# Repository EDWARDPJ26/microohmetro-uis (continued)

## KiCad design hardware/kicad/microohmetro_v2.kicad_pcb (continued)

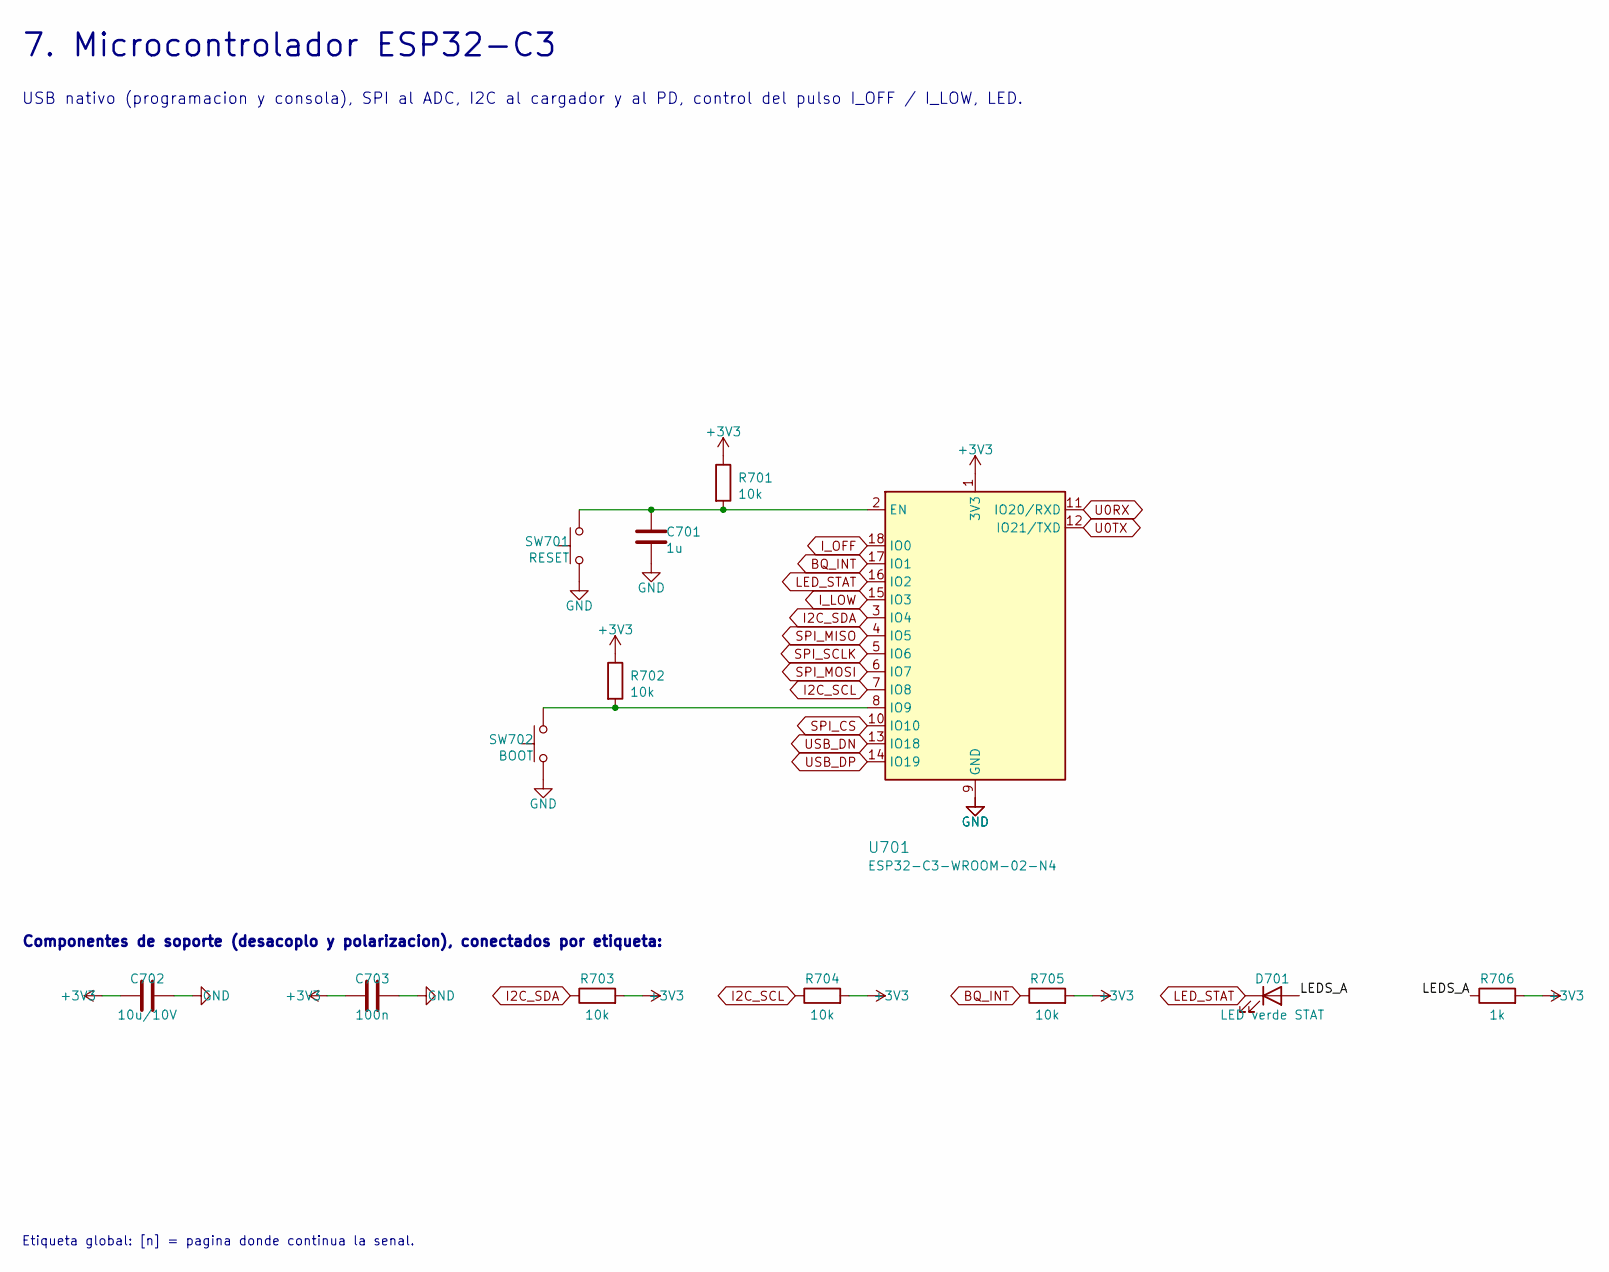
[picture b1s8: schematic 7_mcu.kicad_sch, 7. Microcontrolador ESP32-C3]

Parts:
C701: 1u; C_0603_1608Metric
C702: 10u/10V; C_0805_2012Metric
C703: 100n; C_0603_1608Metric
D701: LED verde STAT; LED_0603_1608Metric
R701, R702, R703, R704, R705: 10k; R_0603_1608Metric
R706: 1k; R_0603_1608Metric
SW701: RESET; SW_Push_SPST_NO_Alps_SKRK
SW702: BOOT; SW_Push_SPST_NO_Alps_SKRK
U701: ESP32-C3-WROOM-02-N4; ESP32-C3-WROOM-02; MPN ESP32-C3-WROOM-02-N4

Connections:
+3V3: C702.1, C703.1, R701.1, R702.1, R703.2, R704.2, R705.2, R706.2, U701.1 (3V3); also elsewhere on the board
BQ_INT: R705.1, U701.17 (IO1); also elsewhere on the board
GND: C701.2, C702.2, C703.2, SW701.1, SW702.1, U701.9 (GND), U701.19 (GND); also elsewhere on the board
I2C_SCL: R704.1, U701.7 (IO8); also elsewhere on the board
I2C_SDA: R703.1, U701.3 (IO4); also elsewhere on the board
I_LOW: U701.15 (IO3); also elsewhere on the board
I_OFF: U701.18 (IO0); also elsewhere on the board
LEDS_A: D701.2 (A), R706.1
LED_STAT: D701.1 (K), U701.16 (IO2)
unnamed: C701.1, R701.2, SW701.2, U701.2 (EN)
unnamed: R702.2, SW702.2, U701.8 (IO9)
SPI_CS: U701.10 (IO10); also elsewhere on the board
SPI_MISO: U701.4 (IO5); also elsewhere on the board
SPI_MOSI: U701.6 (IO7); also elsewhere on the board
SPI_SCLK: U701.5 (IO6); also elsewhere on the board
U0RX: U701.11 (IO20/RXD); also elsewhere on the board
U0TX: U701.12 (IO21/TXD); also elsewhere on the board
USB_DN: U701.13 (IO18); also elsewhere on the board
USB_DP: U701.14 (IO19); also elsewhere on the board

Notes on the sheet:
7. Microcontrolador ESP32-C3
USB nativo (programacion y consola), SPI al ADC, I2C al cargador y al PD, control del pulso I_OFF / I_LOW, LED.
Componentes de soporte (desacoplo y polarizacion), conectados por etiqueta:
Etiqueta global: [n] = pagina donde continua la senal.

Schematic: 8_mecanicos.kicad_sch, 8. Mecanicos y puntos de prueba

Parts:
H801, H802, H803, H804: M3; MountingHole_3.2mm_M3
TP801: TP U0TX; TestPoint_Pad_D1.5mm
TP802: TP U0RX; TestPoint_Pad_D1.5mm
TP803: TP GND; TestPoint_Pad_D1.5mm
TP804: TP SYS; TestPoint_Pad_D1.5mm
TP805: TP VBAT_CHG; TestPoint_Pad_D1.5mm
TP806: TP AVDD; TestPoint_Pad_D1.5mm

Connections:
AVDD: TP806.1; also elsewhere on the board
GND: TP803.1; also elsewhere on the board
SYS: TP804.1; also elsewhere on the board
U0RX: TP802.1; also elsewhere on the board
U0TX: TP801.1; also elsewhere on the board
VBAT_CHG: TP805.1; also elsewhere on the board

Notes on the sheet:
8. Mecanicos y puntos de prueba
Agujeros M3, puntos de prueba y bandera de GND.
Etiqueta global: [n] = pagina donde continua la senal.

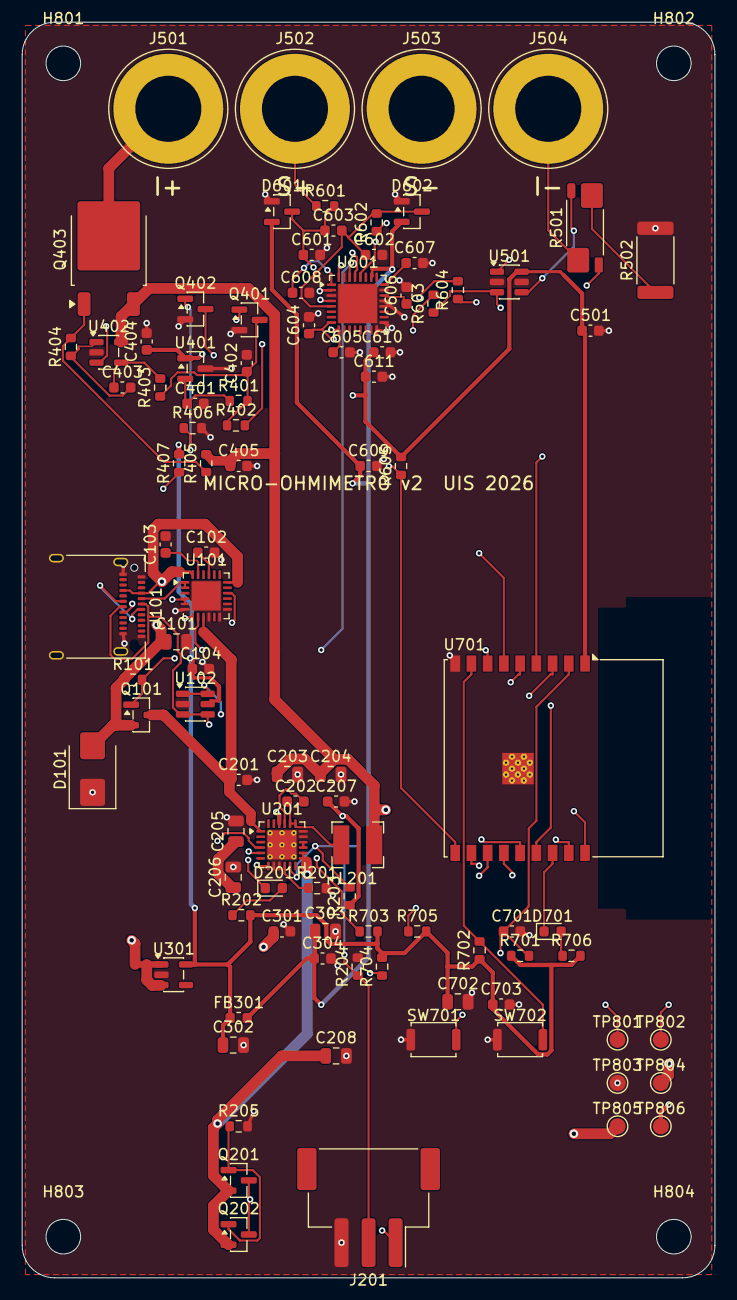
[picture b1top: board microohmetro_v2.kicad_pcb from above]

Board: 4 copper layers, 64.0 x 116.0 mm, 103 parts (1 on the bottom side), 60 nets.

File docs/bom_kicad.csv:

"Reference","Value","Footprint","MPN","Description","QUANTITY"
"C101,C205,C206","10u/25V","Capacitor_SMD:C_0805_2012Metric","","X7R","3"
"C102-C104,C301,C401,C609,C610,C701","1u","Capacitor_SMD:C_0603_1608Metric","","X7R","8"
"C201","1u/25V","Capacitor_SMD:C_0603_1608Metric","","X7R","1"
"C202","47n","Capacitor_SMD:C_0603_1608Metric","","X7R","1"
"C203,C204,C208,C302,C303,C702","10u/10V","Capacitor_SMD:C_0805_2012Metric","","X7R","6"
"C207","4.7u/10V","Capacitor_SMD:C_0603_1608Metric","","X7R","1"
"C304,C404,C405,C501,C606-C608,C611,C703","100n","Capacitor_SMD:C_0603_1608Metric","","X7R","9"
"C402","22n","Capacitor_SMD:C_0603_1608Metric","","C0G (arranque suave)","1"
"C403,C603","10n","Capacitor_SMD:C_0603_1608Metric","","C0G (integrador),C0G diferencial","2"
"C601,C602,C604,C605","1n","Capacitor_SMD:C_0603_1608Metric","","C0G","4"
"D101","SMBJ12A","Diode_SMD:D_SMB","SMBJ12A","TVS 12 V","1"
"D201","LED ambar CHG","LED_SMD:LED_0603_1608Metric","","Indicador de carga","1"
"D601,D602","BAT54S","Package_TO_SOT_SMD:SOT-23","BAT54S","Clamp AIN0,Clamp AIN1","2"
"D701","LED verde STAT","LED_SMD:LED_0603_1608Metric","","","1"
"FB301","600R@100MHz","Inductor_SMD:L_0603_1608Metric","BLM18KG601SN1D","Ferrita de aislamiento analogico","1"
"H801-H804","M3","MountingHole:MountingHole_3.2mm_M3","","Agujero de montaje M3","4"
"J101","USB-C 24p 5 A","Connector_USB:USB_C_Receptacle_Amphenol_12401610E4-2A","Amphenol 12401610E4#2A","Receptaculo USB-C 24 pines (compatible EPR)","1"
"J201","LiPo 1S (JST XH)","Connector_JST:JST_XH_S3B-XH-SM4-TB_1x03-1MP_P2.50mm_Horizontal","S3B-XH-SM4-TB","1 = BAT+, 2 = NTC, 3 = BAT-","1"
"J501","I_PLUS (rojo)","Connector:Banana_Cliff_FCR7350R_S16N-PC_Horizontal","Cliff FCR7350R","Borne banana 4 mm rojo","1"
"J502","S_PLUS (amarillo)","Connector:Banana_Cliff_FCR7350Y_S16N-PC_Horizontal","Cliff FCR7350Y","Borne banana 4 mm amarillo","1"
"J503","S_MINUS (azul)","Connector:Banana_Cliff_FCR7350L_S16N-PC_Horizontal","Cliff FCR7350L","Borne banana 4 mm azul","1"
"J504","I_MINUS (negro)","Connector:Banana_Cliff_FCR7350B_S16N-PC_Horizontal","Cliff FCR7350B","Borne banana 4 mm negro","1"
"L201","2.2u","Inductor_SMD:L_Bourns-SRN4018","SRN4018-2R2M","2,2 uH, Isat >= 3,5 A","1"
"Q101,Q201,Q202","AO3401A","Package_TO_SOT_SMD:SOT-23","AO3401A","Interruptor de VBUS (VBUS_EN_SNK),Polaridad inversa,Polaridad inversa (paralelo)","3"
"Q401,Q402","2N7002","Package_TO_SOT_SMD:SOT-23","2N7002","Q_LOW: selecciona I_L,Q_OFF: corriente apagada por defecto","2"
"Q403","NTD25P03LT4G","Package_TO_SOT_SMD:TO-252-2","NTD25P03LT4G","P-MOS de paso (pulsos 3,5 W / 120 ms)","1"
"R101,R205,R405-R407","100k","Resistor_SMD:R_0603_1608Metric","","Corriente apagada al arrancar,Pull-up de gate,Thick film 1 %","5"
"R201","178","Resistor_SMD:R_0603_1608Metric","","IINMAX = 355/178 = 2,0 A","1"
"R202,R601,R602,R706","1k","Resistor_SMD:R_0603_1608Metric","","Thick film 1 %,Thin film 0,1 % 25 ppm/C","4"
"R203","5.23k","Resistor_SMD:R_0603_1608Metric","","RT1 (datasheet)","1"
"R204","30.1k","Resistor_SMD:R_0603_1608Metric","","RT2 (datasheet)","1"
"R401,R403,R605,R701-R705","10k","Resistor_SMD:R_0603_1608Metric","","Thick film 1 %,Thin film 0,1 % (R_VSET),Thin film 0,1 % (integrador)","8"
"R402","9.31k","Resistor_SMD:R_0603_1608Metric","","Nivel I_L","1"
"R404,R603,R604","100","Resistor_SMD:R_0603_1608Metric","","Thick film 1 %,Thin film 0,1 %","3"
"R501","0.12 1% 4T","Resistor_SMD:R_Shunt_Vishay_WSK2512_6332Metric_T1.19mm","WSK2512R1200FEA","Shunt Kelvin 0,12 Ohm 1 %","1"
"R502","0.68","Resistor_SMD:R_2512_6332Metric","","R_LIFT 1 % 1 W","1"
"SW701","RESET","Button_Switch_SMD:SW_Push_SPST_NO_Alps_SKRK","","","1"
"SW702","BOOT","Button_Switch_SMD:SW_Push_SPST_NO_Alps_SKRK","","","1"
"TH201","10k NTC","Resistor_SMD:R_0603_1608Metric","NCP18XH103F03RB","DNP si la LiPo trae NTC","1"
"TP801","TP U0TX","TestPoint:TestPoint_Pad_D1.5mm","","Punto de prueba","1"
"TP802","TP U0RX","TestPoint:TestPoint_Pad_D1.5mm","","Punto de prueba","1"
"TP803","TP GND","TestPoint:TestPoint_Pad_D1.5mm","","Punto de prueba","1"
"TP804","TP SYS","TestPoint:TestPoint_Pad_D1.5mm","","Punto de prueba","1"
"TP805","TP VBAT_CHG","TestPoint:TestPoint_Pad_D1.5mm","","Punto de prueba","1"
"TP806","TP AVDD","TestPoint:TestPoint_Pad_D1.5mm","","Punto de prueba","1"
"U101","STUSB4500QTR","Package_DFN_QFN:QFN-24-1EP_4x4mm_P0.5mm_EP2.7x2.7mm","STUSB4500QTR","Controlador USB PD sink (PDO2 = 9 V / 2 A)","1"
"U102","USBLC6-2SC6","Package_TO_SOT_SMD:SOT-23-6","USBLC6-2SC6","ESD en D+/D-","1"
"U201","BQ25895RTWR","Package_DFN_QFN:Texas_RTW_WQFN-24-1EP_4x4mm_P0.5mm_EP2.7x2.7mm_ThermalVias","BQ25895RTWR","Cargador buck 1S I2C, 2 A, power-path","1"
"U301","AP2112K-3.3TRG1","Package_TO_SOT_SMD:SOT-23-5","AP2112K-3.3TRG1","LDO 600 mA","1"
"U401","REF3325AIDBZR","Package_TO_SOT_SMD:SOT-23","REF3325AIDBZR","Referencia 2,5 V +-0,15 %, 30 ppm/C","1"
"U402","OPA388IDBVR","Package_TO_SOT_SMD:SOT-23-5","OPA388IDBVR","Lazo zero-drift","1"
"U501","INA181A1IDBVR","Package_TO_SOT_SMD:SOT-23-6","INA181A1IDBVR","Sensado 20 V/V","1"
"U601","AD7124-4BBCPZ-RL7","Package_CSP:LFCSP-32-1EP_5x5mm_P0.5mm_EP3.6x3.6mm","AD7124-4BBCPZ-RL7","ADC sigma-delta 24 bit, PGA 1-128","1"
"U701","ESP32-C3-WROOM-02-N4","RF_Module:ESP32-C3-WROOM-02","ESP32-C3-WROOM-02-N4","MCU RISC-V, BLE 5, USB nativo","1"

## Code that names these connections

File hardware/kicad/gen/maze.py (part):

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    return len(segs), len(vias)


WIDTH = {"PMID": [0.5, 0.3, 0.2], "VBUS_C": [0.3, 0.2], "VBUS_IN": [0.5, 0.3, 0.2], "Net-(J201-Pin_1)": [1.0, 0.6, 0.4]}
for it in range(3):
    pairs = drc_pairs()
    print(f"iteracion {it}: {len(pairs)} conexiones pendientes (sin GND)")
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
